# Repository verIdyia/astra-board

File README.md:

# Astra Board

ESP32-C3 development board built as a documented AI-assisted PCB experiment.

## Status

**Manufacturing paused due to cost (2026-09-10).** The owner reported approximately **US$123 for Standard PCBA** and **US$85 for Economic PCBA** in the 10-board quote discussion, and chose to stop procurement. These are owner-reported figures, not an independently verified complete checkout total; shipping/tax inclusion and complete LED assembly are unconfirmed. No order or payment was submitted.

KiCad ERC and DRC passed with zero reported violations on 2026-09-10. The repository QR is added and independently decoded from the KiCad export. Manufacturing files are in `fab/rev2/`; supplier assembly-preview verification is pending. JLCPCB currently rejects the LED for Economic PCBA; alternative-part eligibility is inconsistent and remains unresolved. The support inquiry is drafted but unsent. Revision 2 includes the electrical-review routing and power-copper repair. USB signal integrity and regulator temperature remain unverified. No hardware has been manufactured or tested.

## Hardware

- 60 × 40 mm, two layers, front-side SMT
- ESP32-C3-WROOM-02, native USB-C, 3.3 V regulator
- Eight addressable RGB LEDs, two user buttons, BOOT and RESET
- Passive buzzer, OLED header, Qwiic connector and GPIO expansion
- 16 SMT BOM lines / 50 assembled components; buzzer and two headers are owner-soldered

Open `hw/astra-board.kicad_pro` with KiCad 10. Local footprint variants are in `lib/Astra.pretty`; the project footprint table resolves them relative to the project.

See `BRIEF.md` for requirements, `parts/DECISIONS.md` for design choices and known limitations, and `log/` for the experiment record. `parts/bom-candidates.csv` records selected parts and sourcing evidence. Firmware and a machine-readable pinout are planned but not yet implemented.

Raw recordings, account responses, intermediate router output and draft manufacturing files are deliberately excluded. This repository is not yet a fabrication release.

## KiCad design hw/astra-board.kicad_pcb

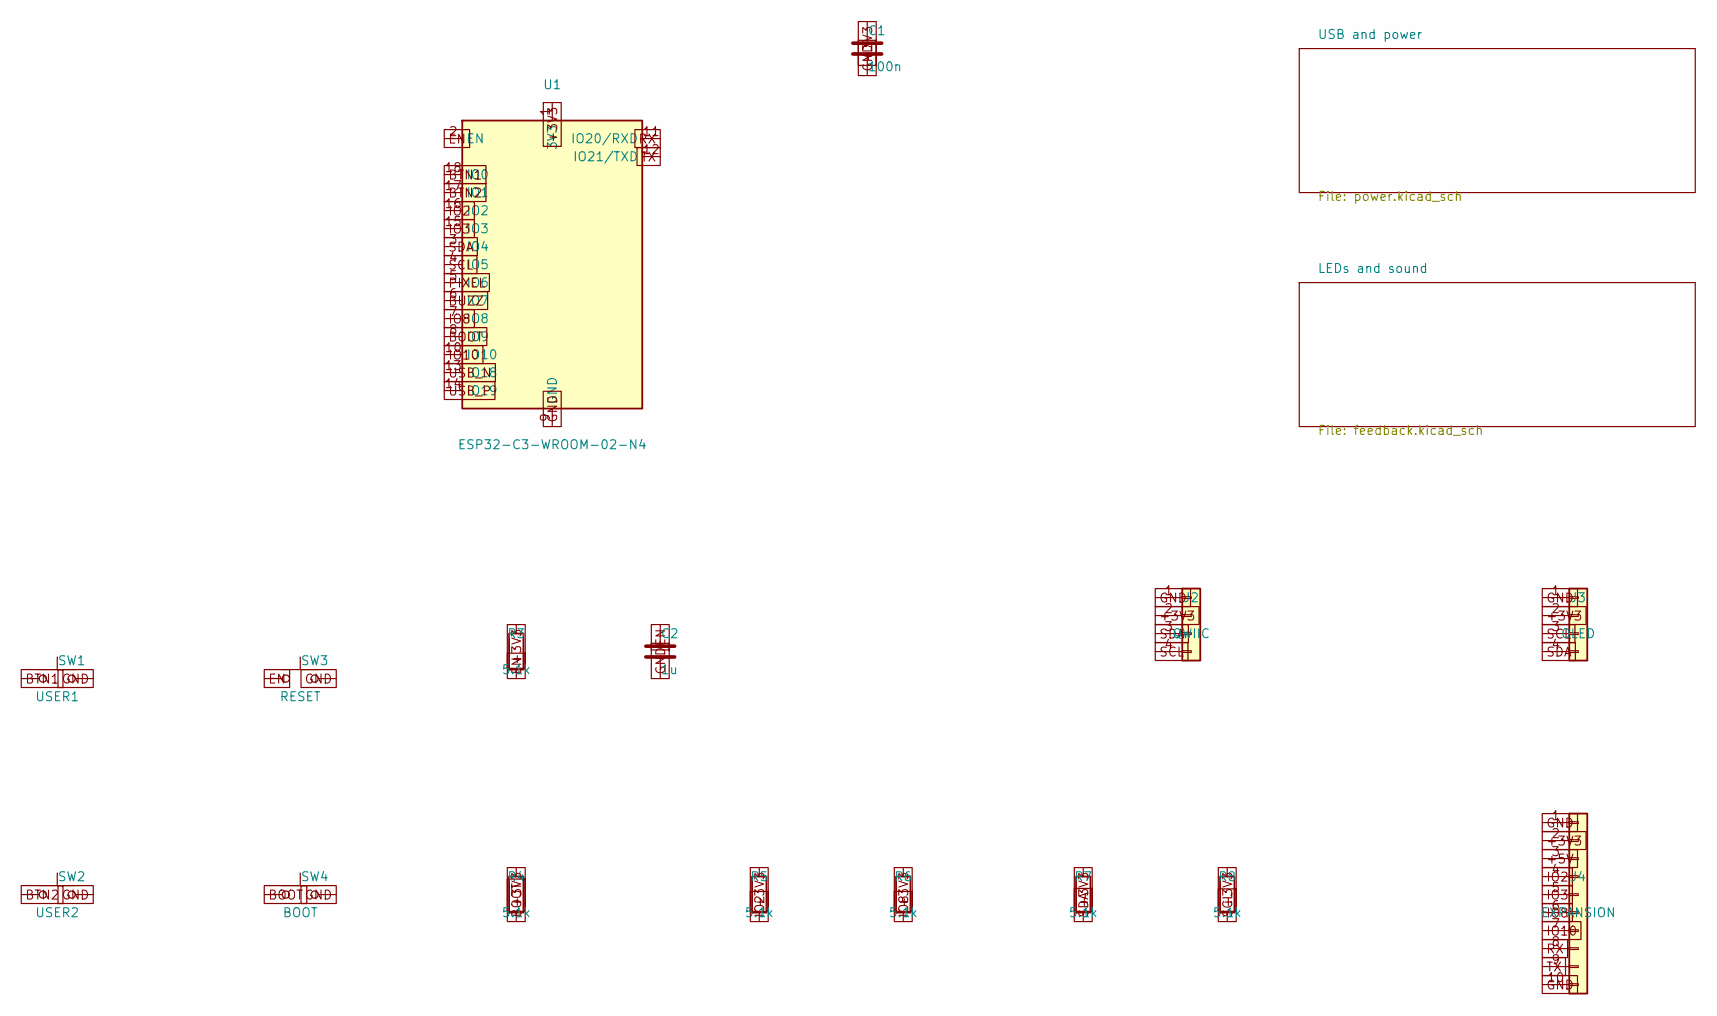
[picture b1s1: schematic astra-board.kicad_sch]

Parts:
C1: 100n; C_0603_1608Metric; MPN CC0603KRX7R9BB104; LCSC C14663
C2: 1u; C_0603_1608Metric; MPN CL10A105KB8NNNC; LCSC C15849
J2: QWIIC; JST_SH_SM04B-SRSS-TB_1x04-1MP_P1.00mm_Horizontal; MPN SM04B-SRSS-TB(LF)(SN); LCSC C160404
J3: OLED; PinHeader_1x04_P2.54mm_Vertical; MPN B-2100S04P-A110; LCSC C124378
J4: EXPANSION; PinHeader_1x10_P2.54mm_Vertical; MPN B-2100S10P-A110; LCSC C124372
R3, R4, R5, R6, R7, R8: 5.1k; R_0603_1608Metric; MPN 0603WAF5101T5E; LCSC C23186
SW1: USER1; SW_SPST_TS-1088-xR020; MPN TS-1088R-02026; LCSC C455280
SW2: USER2; SW_SPST_TS-1088-xR020; MPN TS-1088R-02026; LCSC C455280
SW3: RESET; SW_SPST_TS-1088-xR020; MPN TS-1088R-02026; LCSC C455280
SW4: BOOT; SW_SPST_TS-1088-xR020; MPN TS-1088R-02026; LCSC C455280
U1: ESP32-C3-WROOM-02-N4; ESP32-C3-WROOM-02; MPN ESP32-C3-WROOM-02-N4; LCSC C2934560

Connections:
+3V3: C1.1, J2.2, J3.2, J4.2, R3.1, R4.1, R5.1, R6.1, R7.1, R8.1, U1.1 (3V3); also elsewhere on the board
+5V: J4.3; also elsewhere on the board
BOOT: R4.2, SW4.1, U1.8 (IO9)
BTN1: SW1.1, U1.18 (IO0)
BTN2: SW2.1, U1.17 (IO1)
BUZZ: U1.6 (IO7); also elsewhere on the board
EN: C2.1, R3.2, SW3.1, U1.2 (EN)
GND: C1.2, C2.2, J2.1, J3.1, J4.1, J4.10, SW1.2, SW2.2, SW3.2, SW4.2, U1.9 (GND), U1.19 (GND); also elsewhere on the board
IO2: J4.4, R5.2, U1.16 (IO2)
IO3: J4.5, U1.15 (IO3)
IO8: J4.6, R6.2, U1.7 (IO8)
IO10: J4.7, U1.10 (IO10)
PIXEL: U1.5 (IO6); also elsewhere on the board
RX: J4.8, U1.11 (IO20/RXD)
SCL: J2.4, J3.3, R8.2, U1.4 (IO5)
SDA: J2.3, J3.4, R7.2, U1.3 (IO4)
TX: J4.9, U1.12 (IO21/TXD)
USB_N: U1.13 (IO18); also elsewhere on the board
USB_P: U1.14 (IO19); also elsewhere on the board

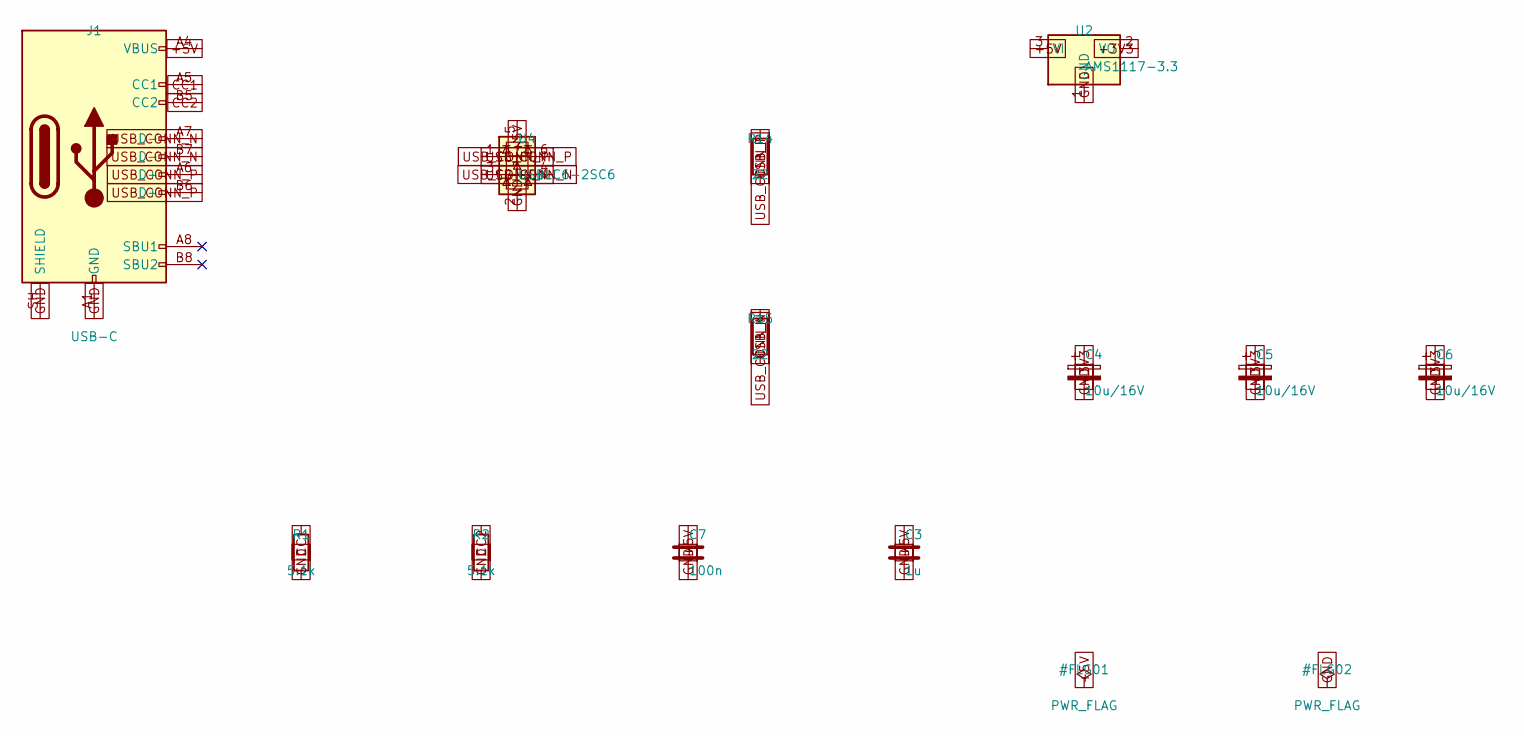
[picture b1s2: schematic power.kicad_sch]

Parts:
C3: 1u; C_0603_1608Metric; MPN CL10A105KB8NNNC; LCSC C15849
C4, C5, C6: 10u/16V; CP_EIA-3216-18_Kemet-A; MPN TAJA106K016RNJ; LCSC C7171
C7: 100n; C_0603_1608Metric; MPN CC0603KRX7R9BB104; LCSC C14663
J1: USB-C; USB_C_Receptacle_HRO_TYPE-C-31-M-12; MPN TYPE-C-31-M-12; LCSC C165948
R1, R2: 5.1k; R_0603_1608Metric; MPN 0603WAF5101T5E; LCSC C23186
R14, R15: 22; R_0603_1608Metric; MPN 0603WAF220JT5E; LCSC C23345
U2: AMS1117-3.3; SOT-223-3_TabPin2; MPN AMS1117-3.3; LCSC C6186
U4: USBLC6-2SC6; SOT-23-6; MPN USBLC6-2SC6; LCSC C7519

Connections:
+3V3: C4.1, C5.1, C6.1, U2.2 (VO); also elsewhere on the board
+5V: C3.1, C7.1, J1.A4 (VBUS), J1.A9 (VBUS), J1.B4 (VBUS), J1.B9 (VBUS), U2.3 (VI), U4.5 (VBUS); also elsewhere on the board
CC1: J1.A5 (CC1), R1.1
CC2: J1.B5 (CC2), R2.1
GND: C3.2, C4.2, C5.2, C6.2, C7.2, J1.A1 (GND), J1.A12 (GND), J1.B1 (GND), J1.B12 (GND), J1.SH (SHIELD), R1.2, R2.2, U2.1 (GND), U4.2 (GND); also elsewhere on the board
USB_CONN_N: J1.A7 (D-), J1.B7 (D-), R15.1, U4.3 (I/O2), U4.4 (I/O2)
USB_CONN_P: J1.A6 (D+), J1.B6 (D+), R14.1, U4.1 (I/O1), U4.6 (I/O1)
USB_N: R15.2; also elsewhere on the board
USB_P: R14.2; also elsewhere on the board

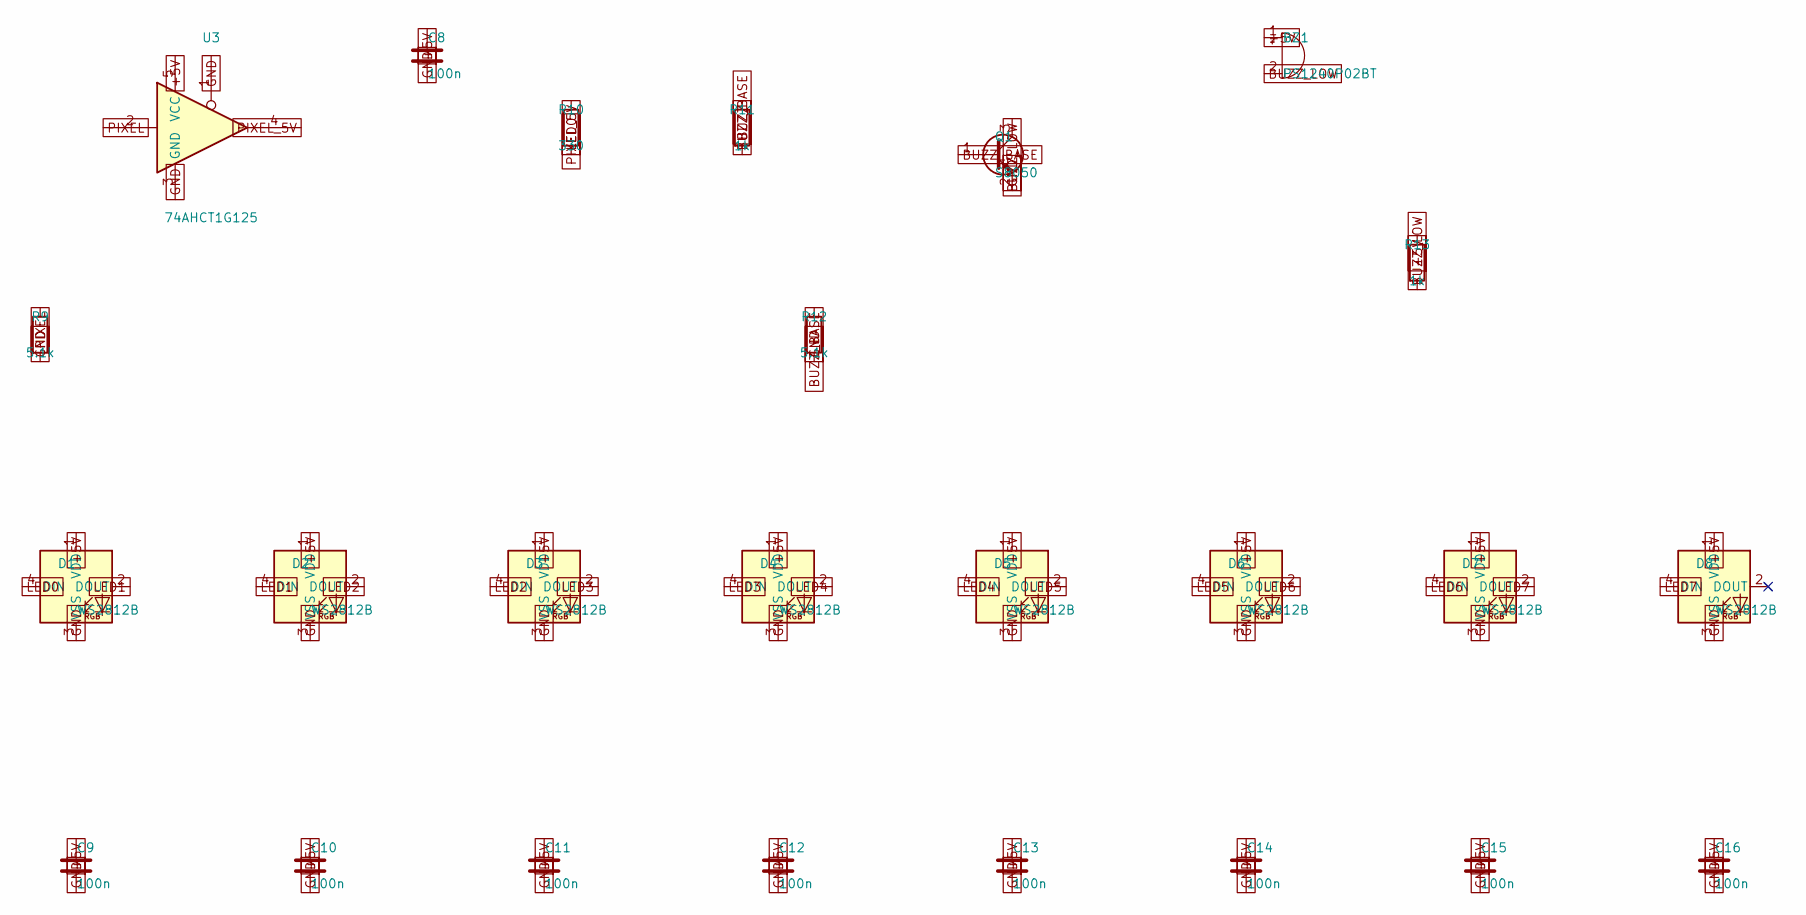
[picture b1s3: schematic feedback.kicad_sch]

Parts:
BZ1: PS1240P02BT; Buzzer_TDK_PS1240P02BT_D12.2mm_H6.5mm; MPN PS1240P02BT; LCSC C76871
C8, C9, C10, C11, C12, C13, C14, C15, C16: 100n; C_0603_1608Metric; MPN CC0603KRX7R9BB104; LCSC C14663
D1, D2, D3, D4, D5, D6, D7, D8: WS2812B; LED_WS2812B_PLCC4_5.0x5.0mm_P3.2mm; MPN WS2812B-V5/W; LCSC C2874885
Q1: S8050; SOT-23; MPN S8050 J3Y(RANGE:200-350); LCSC C2146
R9, R12: 5.1k; R_0603_1608Metric; MPN 0603WAF5101T5E; LCSC C23186
R10: 330; R_0603_1608Metric; MPN 0603WAF3300T5E; LCSC C23138
R11, R13: 1k; R_0603_1608Metric; MPN 0603WAF1001T5E; LCSC C21190
U3: 74AHCT1G125; SOT-23-5; MPN SN74AHCT1G125DBVR; LCSC C7484

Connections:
+5V: BZ1.1 (+), C8.1, C9.1, C10.1, C11.1, C12.1, C13.1, C14.1, C15.1, C16.1, D1.1 (VDD), D2.1 (VDD), D3.1 (VDD), D4.1 (VDD), D5.1 (VDD), D6.1 (VDD), D7.1 (VDD), D8.1 (VDD), R13.1, U3.5 (VCC); also elsewhere on the board
BUZZ: R11.1; also elsewhere on the board
BUZZ_BASE: Q1.1 (B), R11.2, R12.1
BUZZ_LOW: BZ1.2 (-), Q1.3 (C), R13.2
GND: C8.2, C9.2, C10.2, C11.2, C12.2, C13.2, C14.2, C15.2, C16.2, D1.3 (VSS), D2.3 (VSS), D3.3 (VSS), D4.3 (VSS), D5.3 (VSS), D6.3 (VSS), D7.3 (VSS), D8.3 (VSS), Q1.2 (E), R9.2, R12.2, U3.1, U3.3 (GND); also elsewhere on the board
LED0: D1.4 (DIN), R10.2
LED1: D1.2 (DOUT), D2.4 (DIN)
LED2: D2.2 (DOUT), D3.4 (DIN)
LED3: D3.2 (DOUT), D4.4 (DIN)
LED4: D4.2 (DOUT), D5.4 (DIN)
LED5: D5.2 (DOUT), D6.4 (DIN)
LED6: D6.2 (DOUT), D7.4 (DIN)
LED7: D7.2 (DOUT), D8.4 (DIN)
PIXEL: R9.1, U3.2; also elsewhere on the board
PIXEL_5V: R10.1, U3.4

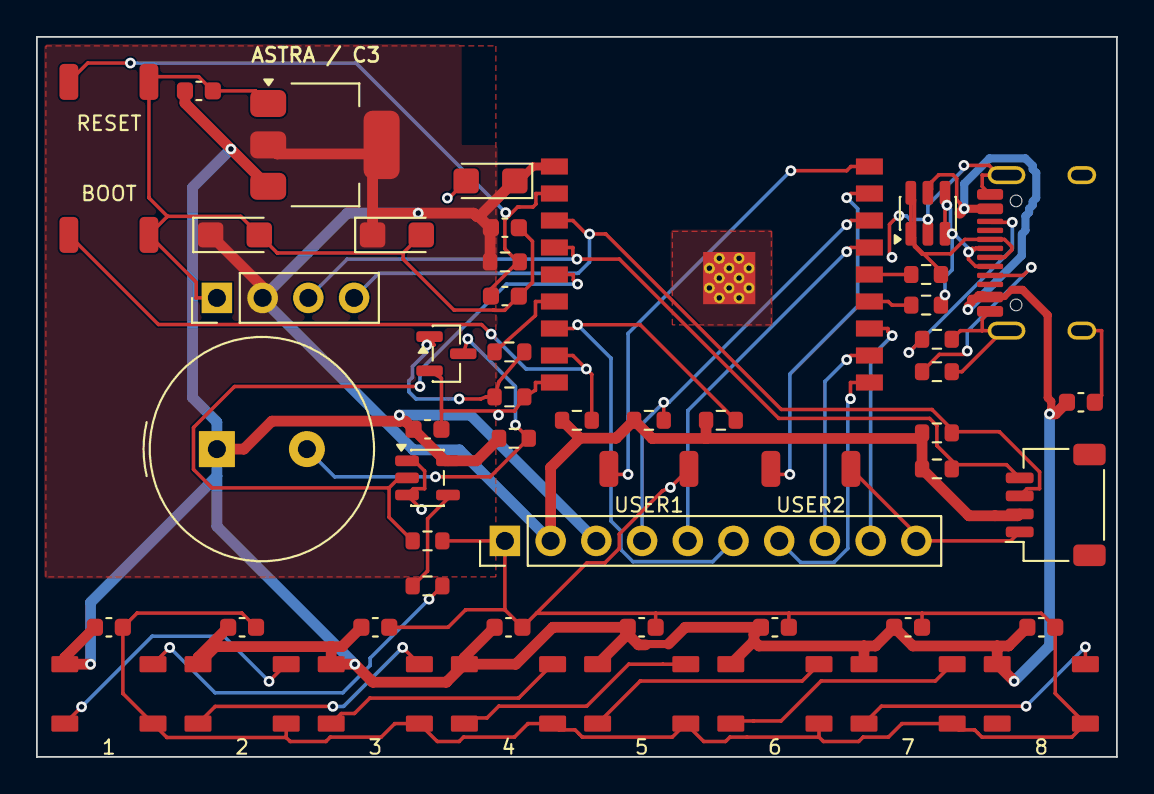
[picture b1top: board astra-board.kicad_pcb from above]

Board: 2 copper layers, 60.0 x 40.0 mm, 53 parts (0 on the bottom side), 34 nets.
